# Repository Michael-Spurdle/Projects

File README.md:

# Projects

A collection of files and photos of projects I have/am working on currently.

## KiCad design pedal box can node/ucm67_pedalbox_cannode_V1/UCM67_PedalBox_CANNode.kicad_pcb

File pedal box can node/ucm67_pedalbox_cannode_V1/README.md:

# UCM67_PedalBox_CANNode

## Getting started

To make it easy for you to get started with GitLab, here's a list of recommended next steps.

Already a pro? Just edit this README.md and make it your own. Want to make it easy? [Use the template at the bottom](#editing-this-readme)!

## Add your files

- [ ] [Create](https://docs.gitlab.com/ee/user/project/repository/web_editor.html#create-a-file) or [upload](https://docs.gitlab.com/ee/user/project/repository/web_editor.html#upload-a-file) files
- [ ] [Add files using the command line](https://docs.gitlab.com/ee/gitlab-basics/add-file.html#add-a-file-using-the-command-line) or push an existing Git repository with the following command:

```
cd existing_repo
git remote add origin https://gitlab.com/ucm-22/pcbs/ucm67_pedalbox_cannode.git
git branch -M main
git push -uf origin main
```

## Integrate with your tools

- [ ] [Set up project integrations](https://gitlab.com/ucm-22/pcbs/ucm67_pedalbox_cannode/-/settings/integrations)

## Collaborate with your team

- [ ] [Invite team members and collaborators](https://docs.gitlab.com/ee/user/project/members/)
- [ ] [Create a new merge request](https://docs.gitlab.com/ee/user/project/merge_requests/creating_merge_requests.html)
- [ ] [Automatically close issues from merge requests](https://docs.gitlab.com/ee/user/project/issues/managing_issues.html#closing-issues-automatically)
- [ ] [Enable merge request approvals](https://docs.gitlab.com/ee/user/project/merge_requests/approvals/)
- [ ] [Automatically merge when pipeline succeeds](https://docs.gitlab.com/ee/user/project/merge_requests/merge_when_pipeline_succeeds.html)

## Test and Deploy

Use the built-in continuous integration in GitLab.

- [ ] [Get started with GitLab CI/CD](https://docs.gitlab.com/ee/ci/quick_start/index.html)
- [ ] [Analyze your code for known vulnerabilities with Static Application Security Testing(SAST)](https://docs.gitlab.com/ee/user/application_security/sast/)
- [ ] [Deploy to Kubernetes, Amazon EC2, or Amazon ECS using Auto Deploy](https://docs.gitlab.com/ee/topics/autodevops/requirements.html)
- [ ] [Use pull-based deployments for improved Kubernetes management](https://docs.gitlab.com/ee/user/clusters/agent/)
- [ ] [Set up protected environments](https://docs.gitlab.com/ee/ci/environments/protected_environments.html)

***

# Editing this README

When you're ready to make this README your own, just edit this file and use the handy template below (or feel free to structure it however you want - this is just a starting point!).  Thank you to [makeareadme.com](https://www.makeareadme.com/) for this template.

## Suggestions for a good README
Every project is different, so consider which of these sections apply to yours. The sections used in the template are suggestions for most open source projects. Also keep in mind that while a README can be too long and detailed, too long is better than too short. If you think your README is too long, consider utilizing another form of documentation rather than cutting out information.

## Name
Choose a self-explaining name for your project.

## Description
Let people know what your project can do specifically. Provide context and add a link to any reference visitors might be unfamiliar with. A list of Features or a Background subsection can also be added here. If there are alternatives to your project, this is a good place to list differentiating factors.

## Badges
On some READMEs, you may see small images that convey metadata, such as whether or not all the tests are passing for the project. You can use Shields to add some to your README. Many services also have instructions for adding a badge.

## Visuals
Depending on what you are making, it can be a good idea to include screenshots or even a video (you'll frequently see GIFs rather than actual videos). Tools like ttygif can help, but check out Asciinema for a more sophisticated method.

## Installation
Within a particular ecosystem, there may be a common way of installing things, such as using Yarn, NuGet, or Homebrew. However, consider the possibility that whoever is reading your README is a novice and would like more guidance. Listing specific steps helps remove ambiguity and gets people to using your project as quickly as possible. If it only runs in a specific context like a particular programming language version or operating system or has dependencies that have to be installed manually, also add a Requirements subsection.

## Usage
Use examples liberally, and show the expected output if you can. It's helpful to have inline the smallest example of usage that you can demonstrate, while providing links to more sophisticated examples if they are too long to reasonably include in the README.

## Support
Tell people where they can go to for help. It can be any combination of an issue tracker, a chat room, an email address, etc.

## Roadmap
If you have ideas for releases in the future, it is a good idea to list them in the README.

## Contributing
State if you are open to contributions and what your requirements are for accepting them.

For people who want to make changes to your project, it's helpful to have some documentation on how to get started. Perhaps there is a script that they should run or some environment variables that they need to set. Make these steps explicit. These instructions could also be useful to your future self.

You can also document commands to lint the code or run tests. These steps help to ensure high code quality and reduce the likelihood that the changes inadvertently break something. Having instructions for running tests is especially helpful if it requires external setup, such as starting a Selenium server for testing in a browser.

## Authors and acknowledgment
Show your appreciation to those who have contributed to the project.

## License
For open source projects, say how it is licensed.

## Project status
If you have run out of energy or time for your project, put a note at the top of the README saying that development has slowed down or stopped completely. Someone may choose to fork your project or volunteer to step in as a maintainer or owner, allowing your project to keep going. You can also make an explicit request for maintainers.

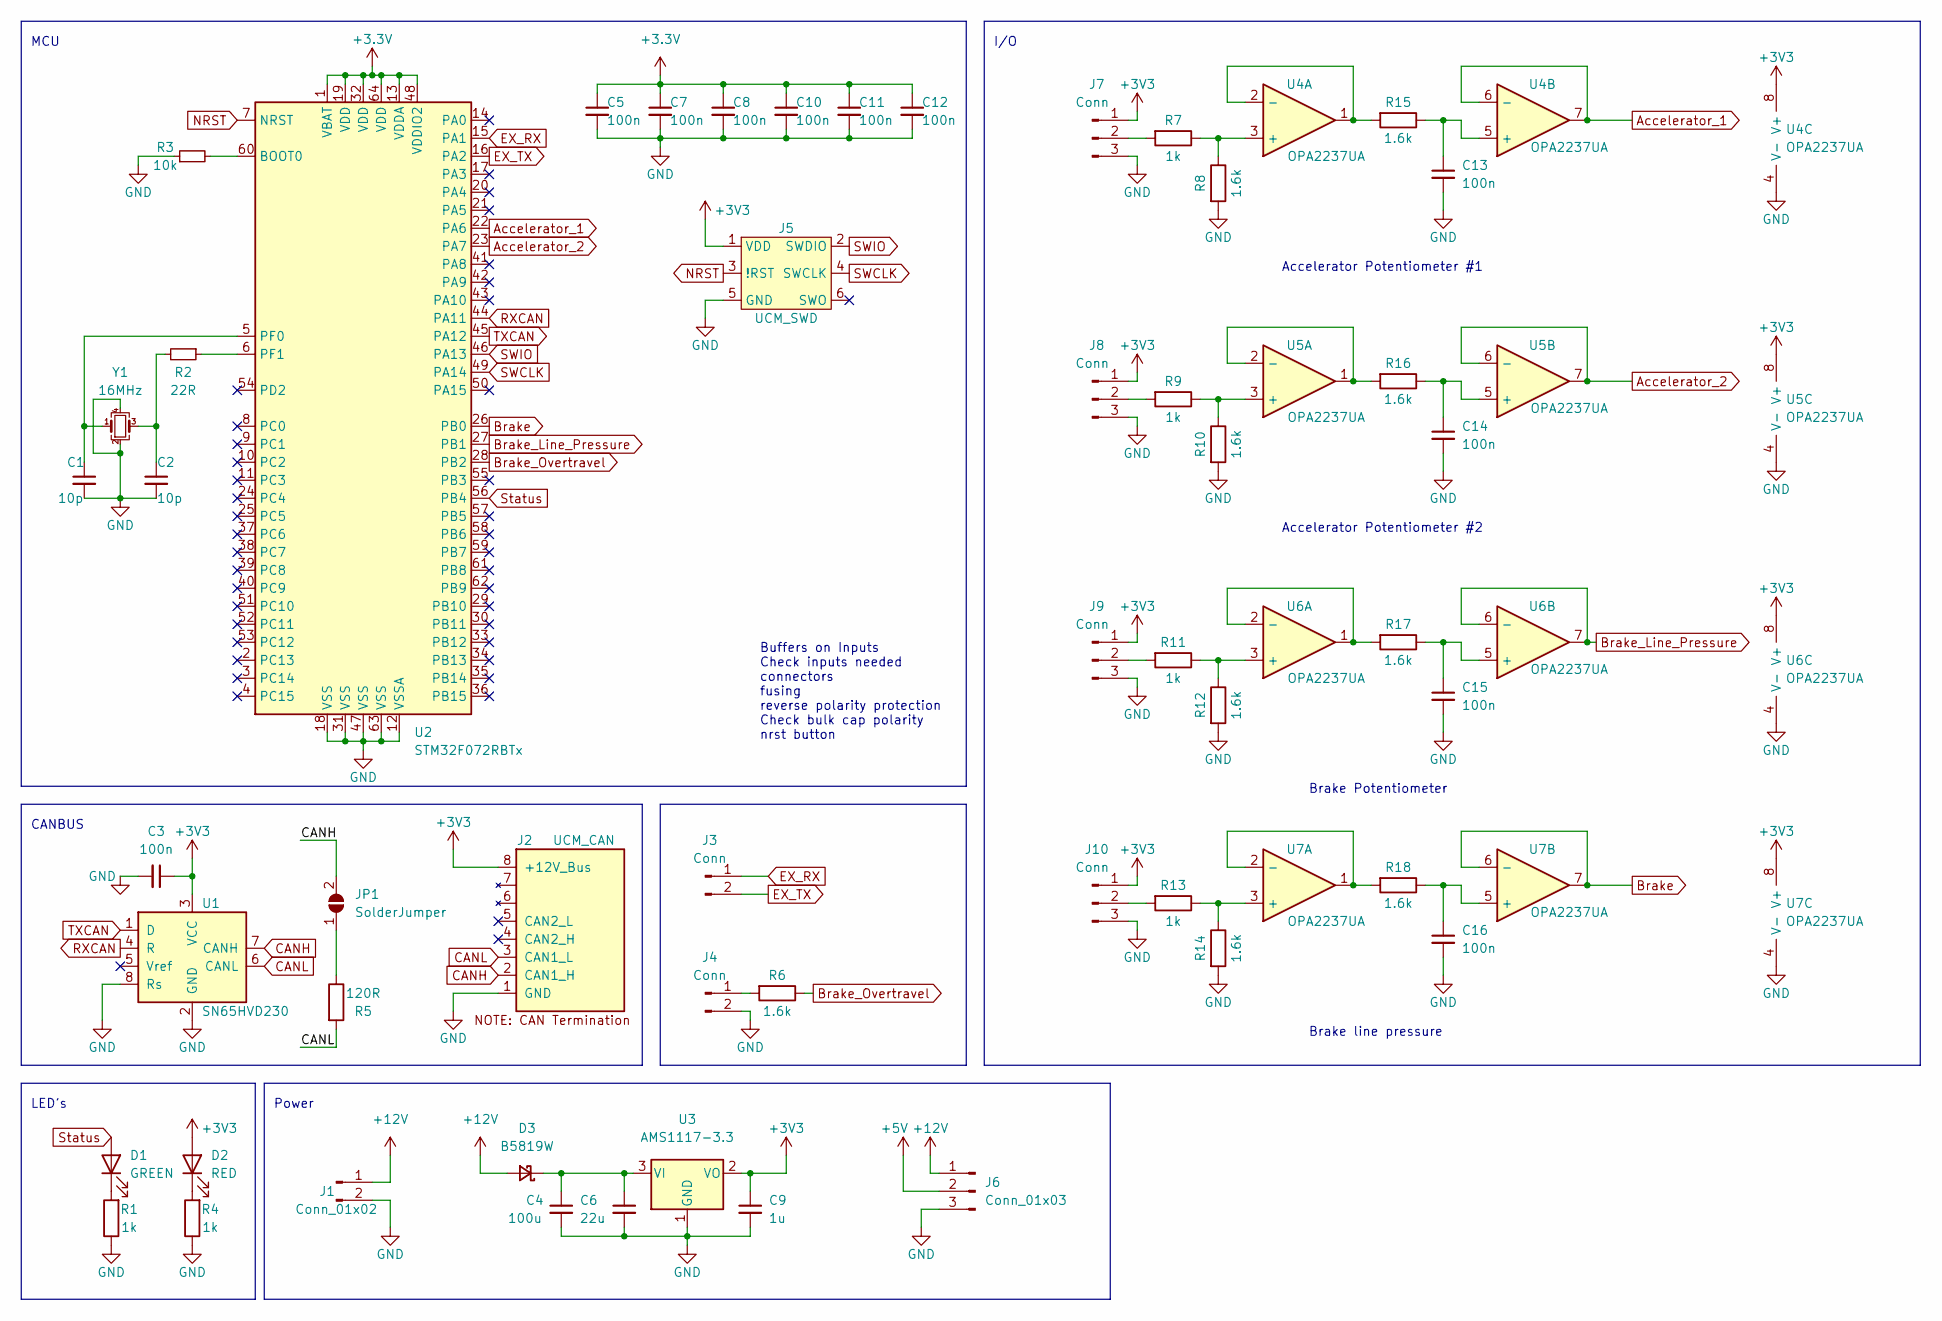
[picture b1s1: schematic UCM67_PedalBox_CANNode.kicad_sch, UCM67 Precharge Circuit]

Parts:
C1, C2: 10p; C_0603_1608Metric
C3, C5, C7, C8, C10, C11, C12: 100n; C_0603_1608Metric
C4: 100u; C_Elec_6.3x7.7
C6: 22u; C_1206_3216Metric
C9: 1u; C_1206_3216Metric
C13, C14, C15, C16: 100n; C_1206_3216Metric
D1: GREEN; LED_0603_1608Metric; LCSC C72043
D2: RED; LED_0603_1608Metric; LCSC C72043
D3: B5819W; D_SOD-123
J1: Conn_01x02; PinHeader_1x02_P2.54mm_Vertical
J2: UCM_CAN; RJ45_Ninigi_GE
J3, J4: Conn; Molex_KK-254_AE-6410-02A_1x02_P2.54mm_Vertical
J5: UCM_SWD; Tag-Connect_TC2030-IDC-NL_2x03_P1.27mm_Vertical
J6: Conn_01x03; PinHeader_1x03_P2.54mm_Vertical
J7, J8, J9, J10: Conn; Molex_KK-254_AE-6410-03A_1x03_P2.54mm_Vertical
JP1: SolderJumper; SolderJumper-2_P1.3mm_Open_RoundedPad1.0x1.5mm
R1, R4: 1k; R_0603_1608Metric
R2: 22R; R_0603_1608Metric
R3: 10k; R_0603_1608Metric
R5: 120R; R_0603_1608Metric
R6, R8, R10, R12, R14, R15, R16, R17, R18: 1.6k; R_1206_3216Metric
R7, R9, R11, R13: 1k; R_1206_3216Metric
U1: SN65HVD230; SOIC-8_3.9x4.9mm_P1.27mm
U2: STM32F072RBTx; LQFP-64_10x10mm_P0.5mm
U3: AMS1117-3.3; SOT-223-3_TabPin2
U4: OPA2237UA; MSOP-8_3x3mm_P0.65mm
U5, U6, U7: OPA2237UA
Y1: 16MHz; Crystal_SMD_0603-4Pin_6.0x3.5mm_HandSoldering

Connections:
+5V: J6.2
+12V: D3.2 (A), J1.1, J6.1
Accelerator_1: U2.22 (PA6), U4.6 (-), U4.7
Accelerator_2: U2.23 (PA7), U5.6 (-), U5.7
Brake: U2.26 (PB0), U7.6 (-), U7.7
Brake_Line_Pressure: U2.27 (PB1), U6.6 (-), U6.7
Brake_Overtravel: R6.1, U2.28 (PB2)
CANH: J2.2 (CAN1_H), JP1.2 (B), U1.7 (CANH)
CANL: J2.3 (CAN1_L), R5.2, U1.6 (CANL)
EX_RX: J3.1, U2.15 (PA1)
EX_TX: J3.2, U2.16 (PA2)
GND: C1.2, C2.2, C3.2, C4.2, C5.2, C6.2, C7.2, C8.2, C9.2, C10.2, C11.2, C12.2, C13.2, C14.2, C15.2, C16.2, J1.2, J2.1 (GND), J4.2, J5.5 (GND), J6.3, J7.3, J8.3, J9.3, J10.3, R1.1, R3.1, R4.1, R8.2, R10.2, R12.2, R14.2, U1.2 (GND), U1.8 (Rs), U2.12 (VSSA), U2.18 (VSS), U2.31 (VSS), U2.47 (VSS), U2.63 (VSS), U3.1 (GND), U4.4 (V-), U5.4 (V-), U6.4 (V-), U7.4 (V-), Y1.2, Y1.4
NRST: J5.3 (!RST), U2.7 (NRST)
unnamed: C1.1, U2.5 (PF0), Y1.1
unnamed: C2.1, R2.2, Y1.3
unnamed: C4.1, C6.1, D3.1 (K), U3.3 (VI)
unnamed: C13.1, R15.1, U4.5 (+)
unnamed: C14.1, R16.1, U5.5 (+)
unnamed: C15.1, R17.1, U6.5 (+)
unnamed: C16.1, R18.1, U7.5 (+)
unnamed: D1.1 (K), R1.2
unnamed: D2.1 (K), R4.2
unnamed: J4.1, R6.2
unnamed: J7.2, R7.2
unnamed: J8.2, R9.2
unnamed: J9.2, R11.2
unnamed: J10.2, R13.2
unnamed: JP1.1 (A), R5.1
unnamed: R2.1, U2.6 (PF1)
unnamed: R3.2, U2.60 (BOOT0)
unnamed: R7.1, R8.1, U4.3 (+)
unnamed: R9.1, R10.1, U5.3 (+)
unnamed: R11.1, R12.1, U6.3 (+)
unnamed: R13.1, R14.1, U7.3 (+)
unnamed: R15.2, U4.1, U4.2 (-)
unnamed: R16.2, U5.1, U5.2 (-)
unnamed: R17.2, U6.1, U6.2 (-)
unnamed: R18.2, U7.1, U7.2 (-)
RXCAN: U1.4 (R), U2.44 (PA11)
SWCLK: J5.4 (SWCLK), U2.49 (PA14)
SWIO: J5.2 (SWDIO), U2.46 (PA13)
Status: D1.2 (A), U2.56 (PB4)
TXCAN: U1.1 (D), U2.45 (PA12)

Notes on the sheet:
I/O
CANBUS
MCU
Accelerator Potentiometer #2
LED's
Brake line pressure
Power
Accelerator Potentiometer #1
Buffers on Inputs Check inputs needed connectors fusing reverse polarity protection Check bulk cap polarity nrst button
Brake Potentiometer

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
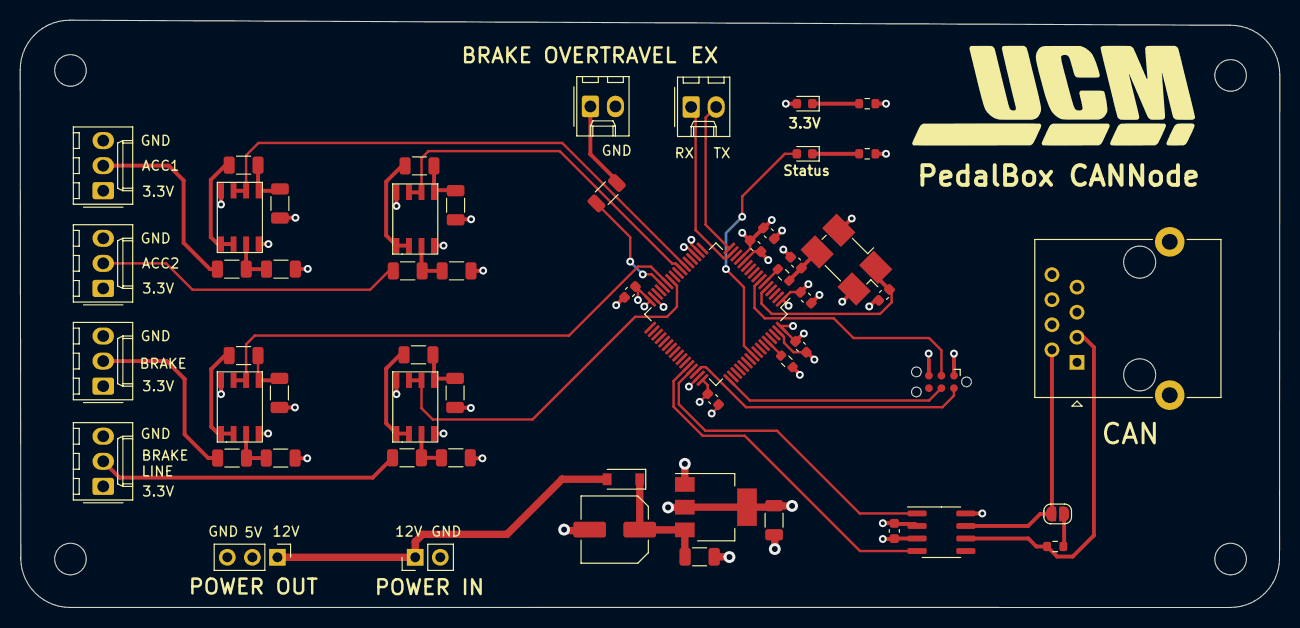
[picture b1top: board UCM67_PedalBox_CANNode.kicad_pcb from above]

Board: 4 copper layers, 127.7 x 59.5 mm, 56 parts (0 on the bottom side), 43 nets.

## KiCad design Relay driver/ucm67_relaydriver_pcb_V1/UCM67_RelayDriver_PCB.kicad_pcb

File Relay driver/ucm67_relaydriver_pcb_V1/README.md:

# UCM67_RelayDriver_PCB

## Getting started

To make it easy for you to get started with GitLab, here's a list of recommended next steps.

Already a pro? Just edit this README.md and make it your own. Want to make it easy? [Use the template at the bottom](#editing-this-readme)!

## Add your files

- [ ] [Create](https://docs.gitlab.com/ee/user/project/repository/web_editor.html#create-a-file) or [upload](https://docs.gitlab.com/ee/user/project/repository/web_editor.html#upload-a-file) files
- [ ] [Add files using the command line](https://docs.gitlab.com/ee/gitlab-basics/add-file.html#add-a-file-using-the-command-line) or push an existing Git repository with the following command:

```
cd existing_repo
git remote add origin https://gitlab.com/ucm-22/pcbs/ucm67_relaydriver_pcb.git
git branch -M main
git push -uf origin main
```

## Integrate with your tools

- [ ] [Set up project integrations](https://gitlab.com/ucm-22/pcbs/ucm67_relaydriver_pcb/-/settings/integrations)

## Collaborate with your team

- [ ] [Invite team members and collaborators](https://docs.gitlab.com/ee/user/project/members/)
- [ ] [Create a new merge request](https://docs.gitlab.com/ee/user/project/merge_requests/creating_merge_requests.html)
- [ ] [Automatically close issues from merge requests](https://docs.gitlab.com/ee/user/project/issues/managing_issues.html#closing-issues-automatically)
- [ ] [Enable merge request approvals](https://docs.gitlab.com/ee/user/project/merge_requests/approvals/)
- [ ] [Automatically merge when pipeline succeeds](https://docs.gitlab.com/ee/user/project/merge_requests/merge_when_pipeline_succeeds.html)

## Test and Deploy

Use the built-in continuous integration in GitLab.

- [ ] [Get started with GitLab CI/CD](https://docs.gitlab.com/ee/ci/quick_start/index.html)
- [ ] [Analyze your code for known vulnerabilities with Static Application Security Testing(SAST)](https://docs.gitlab.com/ee/user/application_security/sast/)
- [ ] [Deploy to Kubernetes, Amazon EC2, or Amazon ECS using Auto Deploy](https://docs.gitlab.com/ee/topics/autodevops/requirements.html)
- [ ] [Use pull-based deployments for improved Kubernetes management](https://docs.gitlab.com/ee/user/clusters/agent/)
- [ ] [Set up protected environments](https://docs.gitlab.com/ee/ci/environments/protected_environments.html)

***

# Editing this README

When you're ready to make this README your own, just edit this file and use the handy template below (or feel free to structure it however you want - this is just a starting point!).  Thank you to [makeareadme.com](https://www.makeareadme.com/) for this template.

## Suggestions for a good README
Every project is different, so consider which of these sections apply to yours. The sections used in the template are suggestions for most open source projects. Also keep in mind that while a README can be too long and detailed, too long is better than too short. If you think your README is too long, consider utilizing another form of documentation rather than cutting out information.

## Name
Choose a self-explaining name for your project.

## Description
Let people know what your project can do specifically. Provide context and add a link to any reference visitors might be unfamiliar with. A list of Features or a Background subsection can also be added here. If there are alternatives to your project, this is a good place to list differentiating factors.

## Badges
On some READMEs, you may see small images that convey metadata, such as whether or not all the tests are passing for the project. You can use Shields to add some to your README. Many services also have instructions for adding a badge.

## Visuals
Depending on what you are making, it can be a good idea to include screenshots or even a video (you'll frequently see GIFs rather than actual videos). Tools like ttygif can help, but check out Asciinema for a more sophisticated method.

## Installation
Within a particular ecosystem, there may be a common way of installing things, such as using Yarn, NuGet, or Homebrew. However, consider the possibility that whoever is reading your README is a novice and would like more guidance. Listing specific steps helps remove ambiguity and gets people to using your project as quickly as possible. If it only runs in a specific context like a particular programming language version or operating system or has dependencies that have to be installed manually, also add a Requirements subsection.

## Usage
Use examples liberally, and show the expected output if you can. It's helpful to have inline the smallest example of usage that you can demonstrate, while providing links to more sophisticated examples if they are too long to reasonably include in the README.

## Support
Tell people where they can go to for help. It can be any combination of an issue tracker, a chat room, an email address, etc.

## Roadmap
If you have ideas for releases in the future, it is a good idea to list them in the README.

## Contributing
State if you are open to contributions and what your requirements are for accepting them.

For people who want to make changes to your project, it's helpful to have some documentation on how to get started. Perhaps there is a script that they should run or some environment variables that they need to set. Make these steps explicit. These instructions could also be useful to your future self.

You can also document commands to lint the code or run tests. These steps help to ensure high code quality and reduce the likelihood that the changes inadvertently break something. Having instructions for running tests is especially helpful if it requires external setup, such as starting a Selenium server for testing in a browser.

## Authors and acknowledgment
Show your appreciation to those who have contributed to the project.

## License
For open source projects, say how it is licensed.

## Project status
If you have run out of energy or time for your project, put a note at the top of the README saying that development has slowed down or stopped completely. Someone may choose to fork your project or volunteer to step in as a maintainer or owner, allowing your project to keep going. You can also make an explicit request for maintainers.

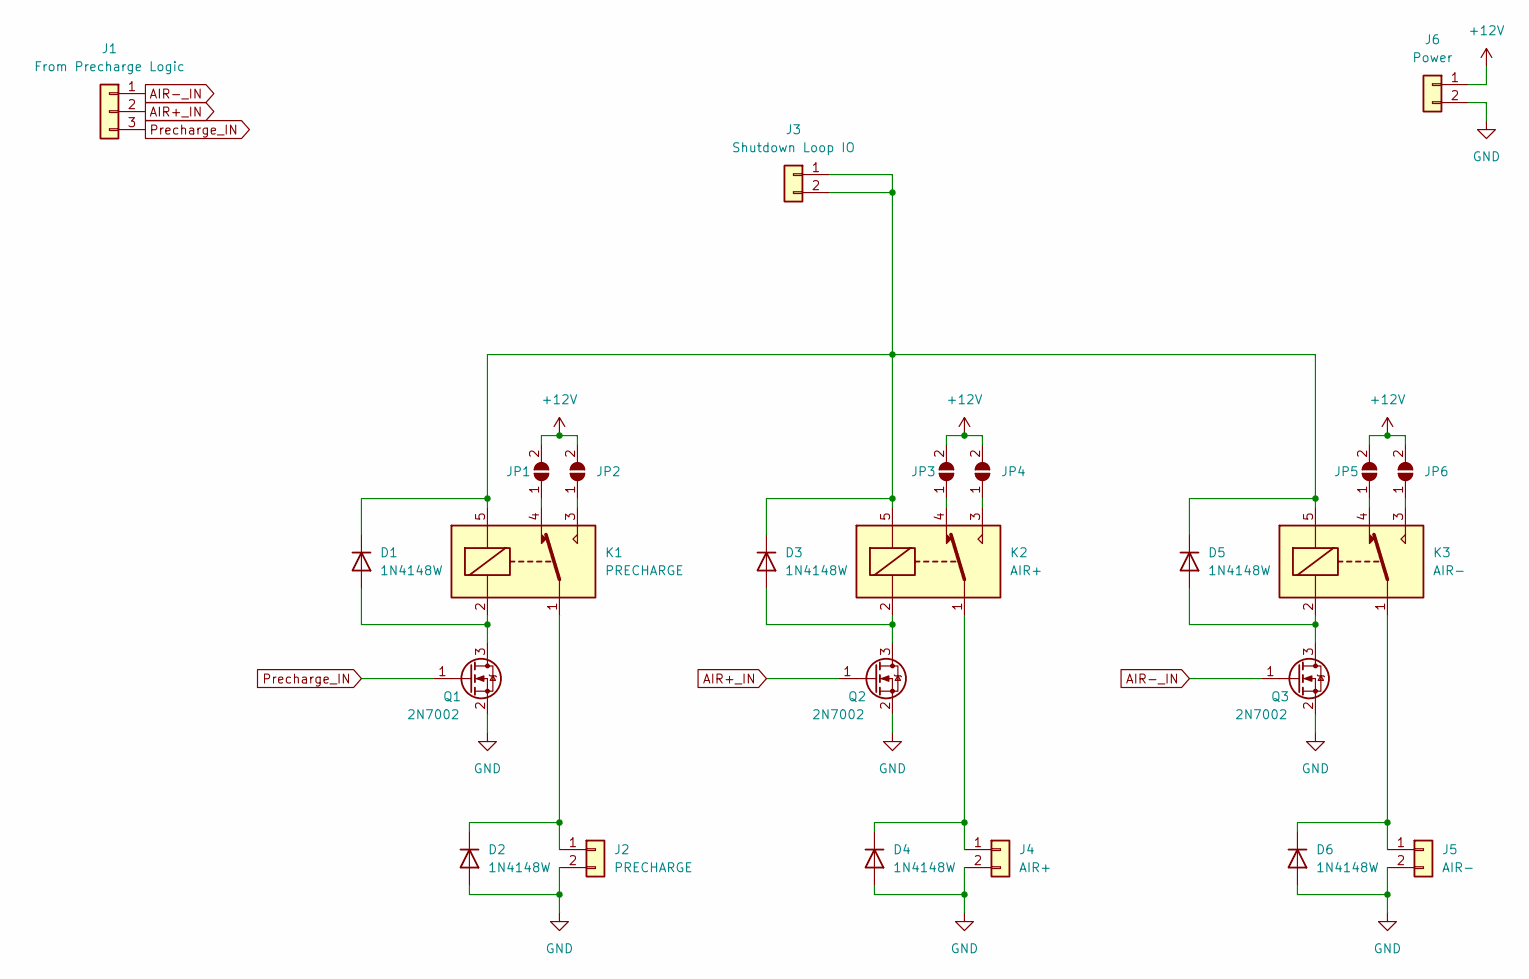
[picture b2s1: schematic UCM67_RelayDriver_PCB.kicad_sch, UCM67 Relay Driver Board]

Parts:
D1, D2, D3, D4, D5, D6: 1N4148W; D_SOD-123
J1: From Precharge Logic; Molex_Micro-Fit_3.0_43650-0300_1x03_P3.00mm_Horizontal
J2: PRECHARGE; Molex_Micro-Fit_3.0_43650-0200_1x02_P3.00mm_Horizontal
J3: Shutdown Loop IO; Molex_Micro-Fit_3.0_43650-0200_1x02_P3.00mm_Horizontal
J4: AIR+; Molex_Micro-Fit_3.0_43650-0200_1x02_P3.00mm_Horizontal
J5: AIR-; Molex_Micro-Fit_3.0_43650-0200_1x02_P3.00mm_Horizontal
J6: Power; Molex_Micro-Fit_3.0_43650-0200_1x02_P3.00mm_Horizontal
JP1, JP2, JP3, JP4, JP5, JP6: SolderJumper_2_Open; SolderJumper-2_P1.3mm_Open_TrianglePad1.0x1.5mm
K1: PRECHARGE; Relay_SPDT_SANYOU_SRD_Series_Form_C
K2: AIR+; Relay_SPDT_SANYOU_SRD_Series_Form_C
K3: AIR-; Relay_SPDT_SANYOU_SRD_Series_Form_C
Q1, Q2, Q3: 2N7002; SOT-23

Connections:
+12V: J6.1, JP1.2 (B), JP2.2 (B), JP3.2 (B), JP4.2 (B), JP5.2 (B), JP6.2 (B)
AIR+_IN: J1.2, Q2.1 (G)
AIR-_IN: J1.1, Q3.1 (G)
GND: D2.2 (A), D4.2 (A), D6.2 (A), J2.2, J4.2, J5.2, J6.2, Q1.2 (S), Q2.2 (S), Q3.2 (S)
unnamed: D1.1 (K), D3.1 (K), D5.1 (K), J3.1, J3.2, K1.5, K2.5, K3.5
unnamed: D1.2 (A), K1.2, Q1.3 (D)
unnamed: D2.1 (K), J2.1, K1.1
unnamed: D3.2 (A), K2.2, Q2.3 (D)
unnamed: D4.1 (K), J4.1, K2.1
unnamed: D5.2 (A), K3.2, Q3.3 (D)
unnamed: D6.1 (K), J5.1, K3.1
unnamed: JP1.1 (A), K1.4
unnamed: JP2.1 (A), K1.3
unnamed: JP3.1 (A), K2.4
unnamed: JP4.1 (A), K2.3
unnamed: JP5.1 (A), K3.4
unnamed: JP6.1 (A), K3.3
Precharge_IN: J1.3, Q1.1 (G)

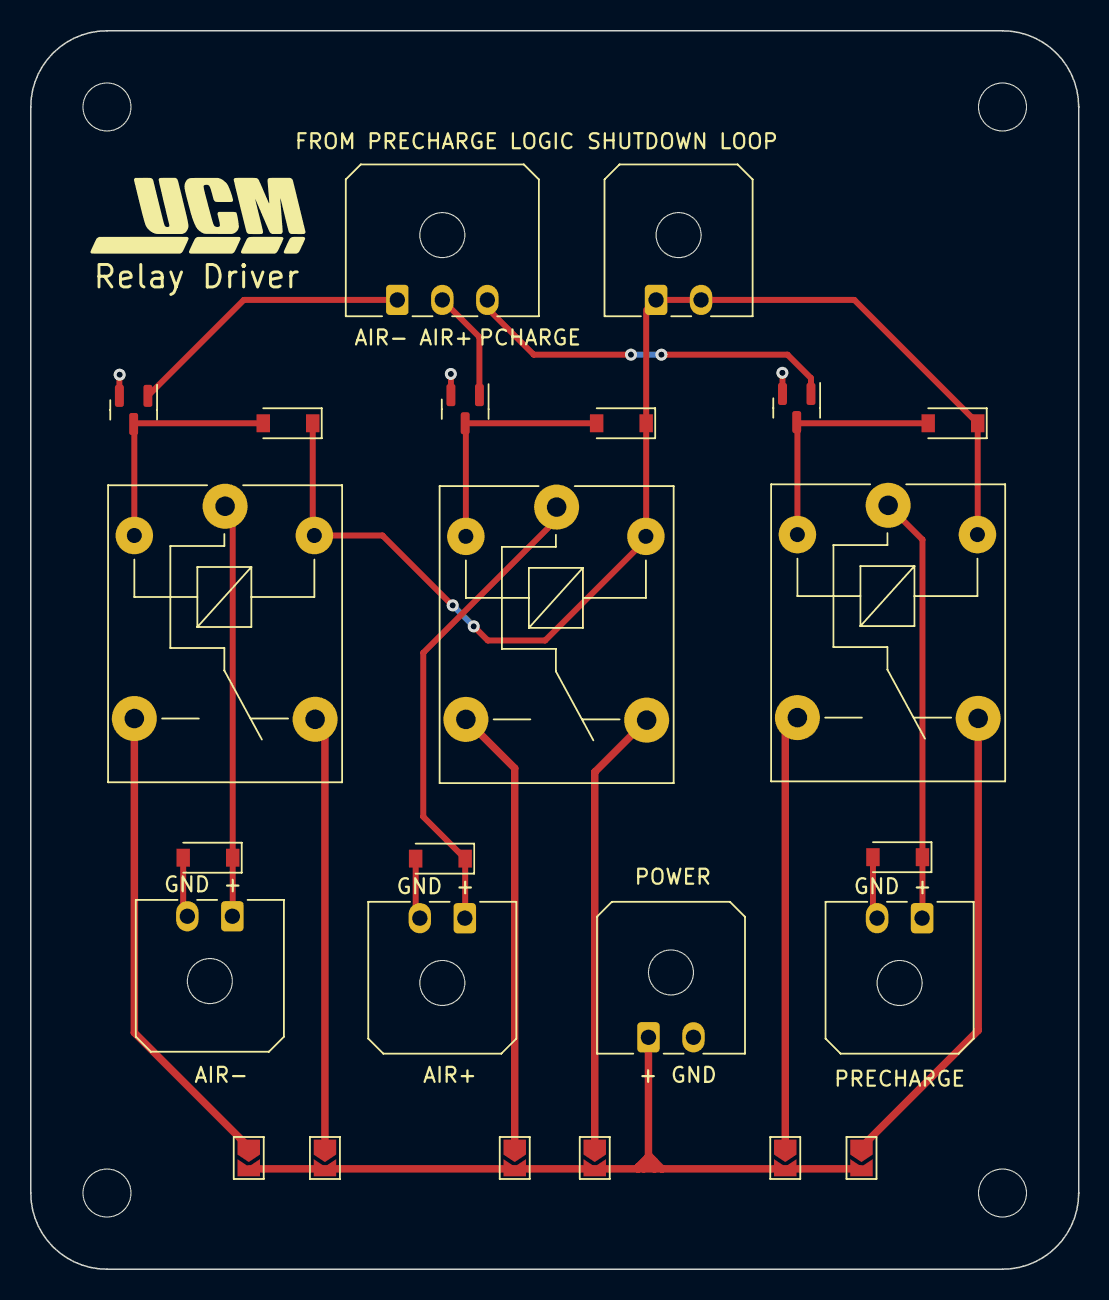
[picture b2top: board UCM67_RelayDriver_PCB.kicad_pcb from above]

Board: 2 copper layers, 69.9 x 82.5 mm, 24 parts (0 on the bottom side), 18 nets.

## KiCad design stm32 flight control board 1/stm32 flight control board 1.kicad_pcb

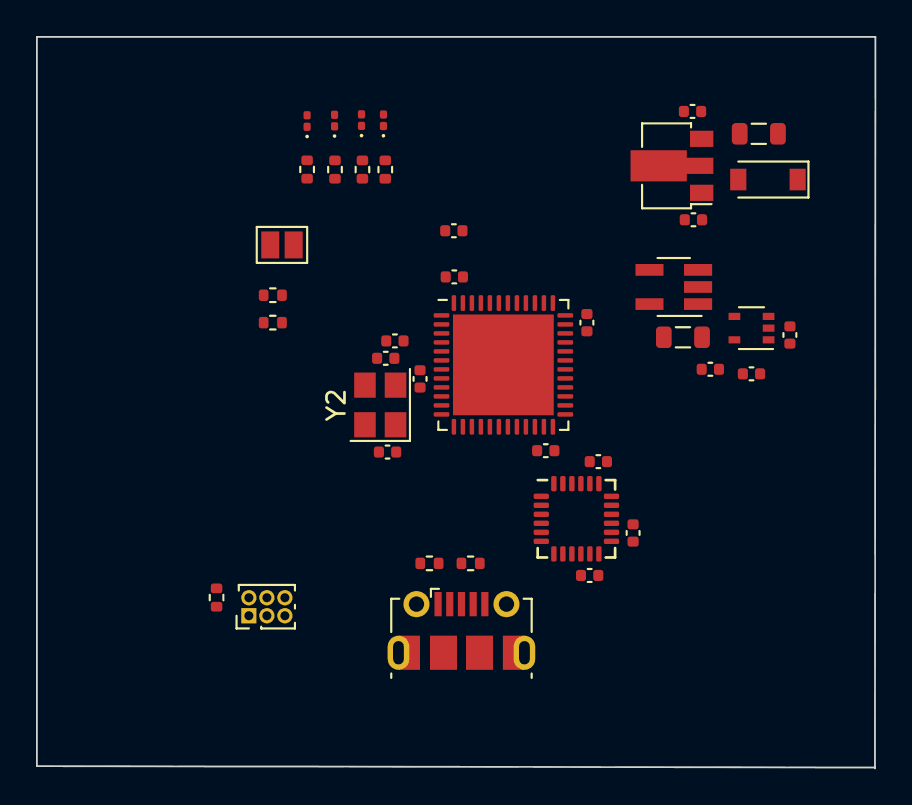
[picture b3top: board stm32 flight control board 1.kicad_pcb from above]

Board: 4 copper layers, 46.6 x 40.6 mm, 41 parts (0 on the bottom side), 35 nets, no tracks yet.

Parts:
C1: 0.33u; C_0402_1005Metric
C2, C4, C5: 0.1u; C_0402_1005Metric
C3: 2.2n; C_0402_1005Metric
C6: 4.7u; C_0402_1005Metric
C7, C9: 10u; C_0402_1005Metric
C8, C10: 1u; C_0402_1005Metric
C11, C12, C13, C14: 100n; C_0402_1005Metric
C15, C22: 20p; C_0402_1005Metric
D1: B5819W; D_SOD-123
D2: CC Dual shottky; SOT-23-5_HandSoldering
D3: GYRO; LED_0201_0603Metric
D4: MCU; LED_0201_0603Metric
D5: 3.3V; LED_0201_0603Metric
D6: 5V; LED_0201_0603Metric
FB1, FB2: GZ2012D101TF; L_0805_2012Metric
J1: SWD; PinHeader_2x03_P1.00mm_Vertical
J2: USB_B_Micro; USB_Micro-B_Molex-105017-0001
R1, R2, R3: 22; R_0402_1005Metric
R4, R7: 47k; R_0402_1005Metric
R8, R9, R10, R11: 1.2k; R_0402_1005Metric
SW1: SW_SPST; SolderJumper-2_P1.3mm_Open_Pad1.0x1.5mm
U1: MPU-6000; InvenSense_QFN-24_4x4mm_P0.5mm
U2: 78L05G-AB3-R; SOT-89-3
U3: MIC5253; SOT-353_SC-70-5
U4: STM32F411CEU6; QFN-48-1EP_7x7mm_P0.5mm_EP5.6x5.6mm
Y2: YSX321SL; Crystal_SMD_3225-4Pin_3.2x2.5mm

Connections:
3.3V: C4.2, C9.1, C10.1, C11.1, C12.1, C13.1, C14.1, J1.1, R10.1, SW1.2 (B), U1.13 (VDD), U3.5 (OUT), U4.1 (VBAT), U4.9 (VDDA), U4.24 (VDD), U4.36 (VDD), U4.48 (VDD)
5V: C5.1, D2.1 (K), R11.1, U2.1 (OUT)
+5VA: D2.3 (K), J2.1 (VBUS)
GND: C1.2, C2.2, C3.2, C4.1, C5.2, C6.2, C7.2, C8.2, C9.2, C10.2, C11.2, C12.2, C13.2, C14.2, C15.2, C22.2, D3.1 (K), D4.1 (K), D5.1 (K), D6.1 (K), J1.3, J1.5, J2.5 (GND), J2.6 (Shield), R4.2, U1.1 (CLKIN), U1.11 (FSYNC), U1.18 (GND), U2.2 (GND), U3.2 (GND), U4.8 (VSSA), U4.23 (VSS), U4.35 (VSS), U4.47 (VSS), U4.49 (VSS)
HSE_IN: C15.1, U4.5 (PH0), Y2.1
HSE_OUT: C22.1, U4.6 (PH1), Y2.2
LED0: R8.1, U4.2 (PC13)
LED1: R9.1, U4.3 (PC14)
MISO: U1.9 (AD0/MISO), U4.16 (PA6)
MOSI: U1.24 (SDA/MOSI), U4.17 (PA7)
MPU EXTI: U1.12 (INT), U4.18 (PB0)
NSS: U1.8 (~CS), U4.14 (PA4)
NSS2: U4.25 (PB12), U4.26 (PB13)
unnamed: C1.1, FB1.2, U2.3 (IN)
unnamed: C2.1, U1.10 (REGOUT)
unnamed: C3.1, U1.20 (CPOUT)
unnamed: C6.1, U4.22 (VCAP1)
unnamed: C7.1, U3.4 (BYP)
unnamed: C8.1, FB2.2, U3.1 (VIN)
unnamed: D3.2 (A), R8.2
unnamed: D4.2 (A), R9.2
unnamed: D5.2 (A), R10.2
unnamed: D6.2 (A), R11.2
unnamed: J1.2, R1.1
unnamed: J2.2 (D-), R3.1
unnamed: J2.3 (D+), R2.1
unnamed: R4.1, R7.1, SW1.1 (A)
unnamed: R7.2, U4.44 (BOOT0)
RESET: D2.2 (A), FB2.1
SCLK: U1.23 (SCL/SCLK), U4.15 (PA5)
SWCLK: J1.4, U4.37 (PA14)
SWDIO: R1.2, U4.34 (PA13)
SWO: J1.6, U4.39 (PB3)
USB D+: R2.2, U4.33 (PA12)
USB D-: R3.2, U4.32 (PA11)

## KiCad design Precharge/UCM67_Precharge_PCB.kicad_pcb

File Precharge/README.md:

# UCM67_Precharge_PCB

## Precharge PCB Functionality

This PCB does...

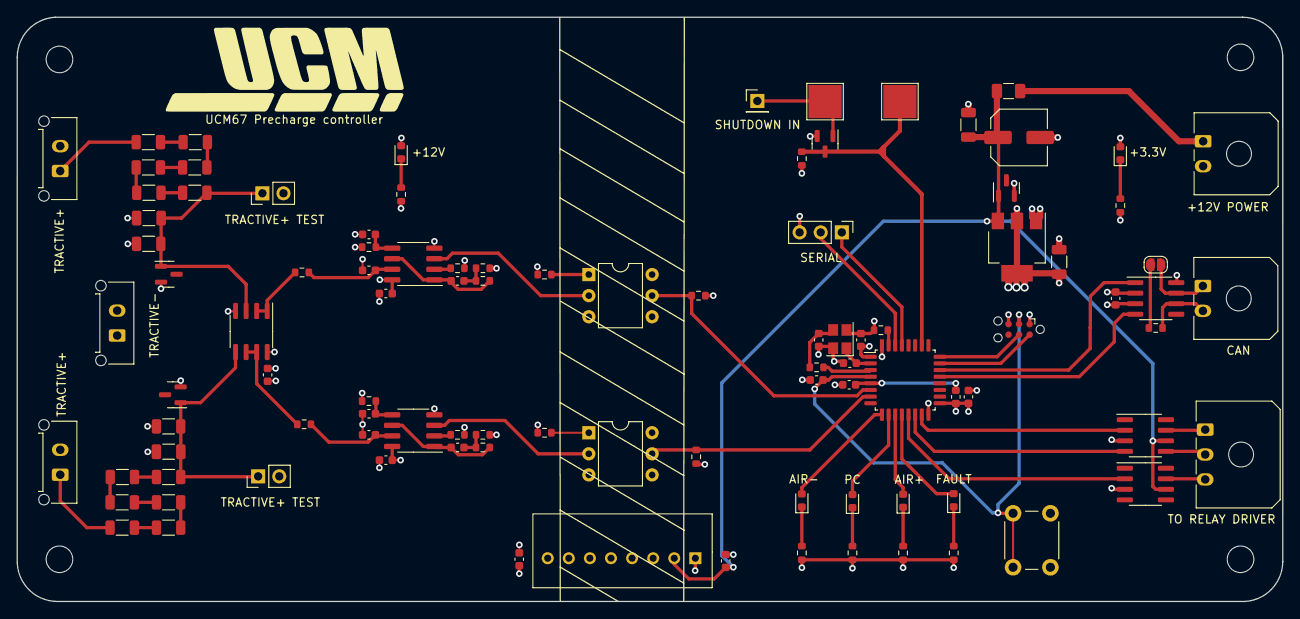
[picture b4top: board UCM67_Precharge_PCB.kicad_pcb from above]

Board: 4 copper layers, 152.4 x 70.4 mm, 100 parts (0 on the bottom side), 71 nets.

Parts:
C1, C4, C8, C9: 1u; C_0603_1608Metric
C2, C3: 100n; C_1206_3216Metric
C5, C6, C7, C11, C12, C19, C20, C21, C22, C23: 100n; C_0603_1608Metric
C10: 100u; C_Elec_6.3x7.7
C13, C14: 10n; C_0603_1608Metric
C15: 22u; C_1206_3216Metric
C16: 1u; C_1206_3216Metric
C17, C18: 10p; C_0603_1608Metric
D1, D5, D7, D9: GREEN; LED_0603_1608Metric
D2: YELLOW; LED_0603_1608Metric
D3, D4, D8: BZX84C12; SOT-23
D6: RED; LED_0603_1608Metric
F1: 2A 0603; Fuse_1206_3216Metric
FB1: Bead; L_0603_1608Metric
J1, J3: Tractive+; Molex_Micro-Fit_3.0_43650-0215_1x02_P3.00mm_Vertical
J2: Tractive-; Molex_Micro-Fit_3.0_43650-0215_1x02_P3.00mm_Vertical
J4: To Relay Driver; Molex_Micro-Fit_3.0_43650-0300_1x03_P3.00mm_Horizontal
J5, J6: Tractive+ TEST; PinHeader_1x02_P2.54mm_Vertical
J7: Conn_01x02; Molex_Micro-Fit_3.0_43650-0200_1x02_P3.00mm_Horizontal
J8: UCM_SWD; Tag-Connect_TC2030-IDC-NL_2x03_P1.27mm_Vertical
J9: SHUTDOWN_IN; PinHeader_1x01_P2.54mm_Vertical
J10: SERIAL; PinHeader_1x03_P2.54mm_Vertical
J12: CAN; Molex_Micro-Fit_3.0_43650-0200_1x02_P3.00mm_Horizontal
JP1: SolderJumper; SolderJumper-2_P1.3mm_Open_RoundedPad1.0x1.5mm
Q3: 2N7002; SOT-23
R1, R2, R3, R4, R5, R6, R8, R9, R10, R11, R13, R14: 510k; R_1206_3216Metric
R7, R12, R17, R18, R21, R32, R33, R34: 1k; R_0603_1608Metric
R15, R16: 39k; R_1206_3216Metric
R19, R20, R22, R23: 100k; R_0603_1608Metric
R24, R25: 47R; R_0603_1608Metric
R26, R27: 12k; R_0603_1608Metric
R28, R29: 6.8k; R_0603_1608Metric
R30, R31: 680R; R_0603_1608Metric
R36: 22R; R_0603_1608Metric
R37, R39: 10k; R_0603_1608Metric
R40: 120R; R_0603_1608Metric
SW1: SW_Push; SW_PUSH_6mm
TP1: Shutdown_IN; TestPoint_Pad_4.0x4.0mm
TP2: Shutdown_State; TestPoint_Pad_4.0x4.0mm
U1: SPAN02; SIP-8
U2: LM2904B; SOIC-8_3.9x4.9mm_P1.27mm
U3, U4: LM331; SOP-8_3.76x4.96mm_P1.27mm
U5: AMS1117-3.3; SOT-223-3_TabPin2
U6, U7: 4N35; DIP-6_W7.62mm
U8: SN65HVD230; SOIC-8_3.9x4.9mm_P1.27mm
U9: STM32F042K6Tx; LQFP-32_7x7mm_P0.8mm
U10, U11: TC4424; SOIC-8_3.9x4.9mm_P1.27mm
Y1: 16MHz; Crystal_SMD_SeikoEpson_FA238-4Pin_3.2x2.5mm

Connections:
+3.3VA: C22.2, FB1.2, U9.5 (VDDA)
+3V3: C16.1, C20.1, C21.1, C23.1, D9.2 (A), FB1.1, J8.1 (VDD), R33.2, R34.2, R39.2, U5.2 (VO), U8.3 (VCC), U9.1 (VDD), U9.17 (VDDIO2)
+12V: C1.1, C10.1, C15.1, D8.1 (K), F1.2, U1.2 (+Vin), U5.3 (VI), U10.6 (VDD), U11.6 (VDD)
+12VA: C4.1, C5.1, C11.1, C12.1, D7.2 (A), R28.2, R29.2, R30.2, R31.2, U1.6 (+Vout), U2.8 (V+), U3.8 (VS), U4.8 (VS)
AIR+: J4.2, U10.5 (OUTB)
AIR+_ON: D5.2 (A), U9.11 (PA5)
AIR-: J4.1, U10.7 (OUTA)
AIR-_ON: D1.2 (A), U9.9 (PA3)
Accumulator_F(V): R34.1, U7.5, U9.7 (PA1)
CANH: J12.1, JP1.2 (B), U8.7 (CANH)
CANL: J12.2, R40.2, U8.6 (CANL)
EN_AIR+: U9.14 (PB0), U10.4 (INB)
EN_AIR-: U9.15 (PB1), U10.2 (INA)
EN_Precharge: U9.13 (PA7), U11.2 (INA)
EX_RX: J10.2, U9.30 (PB7)
EX_TX: J10.1, U9.29 (PB6)
Fault: D6.2 (A), U9.12 (PA6)
GND: C1.2, C10.2, C15.2, C16.2, C17.2, C18.2, C19.2, C20.2, C21.2, C22.1, C23.2, D8.2 (A), J7.2, J8.5 (GND), J10.3, Q3.2 (S), R7.1, R12.1, R17.1, R18.1, R32.1, R37.1, SW1.1, U1.1 (-Vin), U5.1 (GND), U6.4, U7.4, U8.2 (GND), U8.8 (Rs), U9.16 (VSS), U9.32 (VSSA), U10.3 (GND), U11.3 (GND), Y1.2, Y1.4
GNDA: C2.2, C3.2, C4.2, C5.2, C6.2, C7.2, C11.2, C12.2, C13.2, C14.2, D3.2 (A), D4.2 (A), J2.2, J5.2, J6.2, R15.2, R16.2, R21.1, R24.1, R25.1, R26.1, R27.1, U1.7 (-Vout), U2.4 (V-), U3.4 (GND), U4.4 (GND)
NRST: C19.1, J8.3 (!RST), SW1.2, U9.4 (NRST)
unnamed: C2.1, D3.1 (K), J5.1, R13.2, R15.1, U2.3 (+)
unnamed: C3.1, D4.1 (K), J6.1, R14.2, R16.1, U2.5 (+)
unnamed: C6.1, R19.2, U3.7 (CIN)
unnamed: C7.1, R20.2, U4.7 (CIN)
unnamed: C8.1, R22.2, U3.1 (IOUT), U3.6 (THR)
unnamed: C8.2, R22.1, R24.2
unnamed: C9.1, R23.2, U4.1 (IOUT), U4.6 (THR)
unnamed: C9.2, R23.1, R25.2
unnamed: C13.1, R28.1, U3.5 (RC)
unnamed: C14.1, R29.1, U4.5 (RC)
unnamed: C17.1, U9.2 (PF0), Y1.1
unnamed: C18.1, R36.2, Y1.3
unnamed: D1.1 (K), R7.2
unnamed: D2.1 (K), R12.2
unnamed: D5.1 (K), R17.2
unnamed: D6.1 (K), R18.2
unnamed: D7.1 (K), R21.2
unnamed: D9.1 (K), R32.2
unnamed: F1.1, J7.1
unnamed: J1.1, R1.1
unnamed: J3.1, R2.1
unnamed: J9.1, Q3.1 (G), TP1.1
unnamed: JP1.1 (A), R40.1
unnamed: R1.2, R3.1
unnamed: R2.2, R4.1
unnamed: R3.2, R5.1
unnamed: R4.2, R6.1
unnamed: R5.2, R8.1
unnamed: R6.2, R9.1
unnamed: R8.2, R10.1
unnamed: R10.2, R13.1
unnamed: R9.2, R11.1
unnamed: R11.2, R14.1
unnamed: R19.1, U2.1, U2.2 (-)
unnamed: R20.1, U2.6 (-), U2.7
unnamed: R26.2, U3.2 (IREF)
unnamed: R27.2, U4.2 (IREF)
unnamed: R30.1, U6.1
unnamed: R31.1, U7.1
unnamed: R36.1, U9.3 (PF1)
unnamed: R37.2, U9.31 (PB8)
unnamed: U3.3 (FOUT), U6.2
unnamed: U4.3 (FOUT), U7.2
PC_ON: D2.2 (A), U9.10 (PA4)
Precharge: J4.3, U11.7 (OUTA)
RXCAN: U8.4 (R), U9.21 (PA11)
SWCLK: J8.4 (SWCLK), U9.24 (PA14)
SWIO: J8.2 (SWDIO), U9.23 (PA13)
Shutdown_State: Q3.3 (D), R39.1, TP2.1, U9.26 (PB3)
TXCAN: U8.1 (D), U9.22 (PA12)
Tractive_F(V): R33.1, U6.5, U9.6 (PA0)

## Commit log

2022-07-31 Add files via upload
    Initial schematic for the stm32 flight controller board for a FPV drone
2022-07-31 Add files via upload
    PCB's I did the layout for but did not design the schematics
2022-07-31 Add files via upload
    PCB that I have soldered. Not designed by me.
2023-07-09 Add files via upload
    Sim racing wheel photos
